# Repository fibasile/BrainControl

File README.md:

BrainControl
============

Arduino Mind Controlled Robot

Bill of materials
-----------------

- Arduino UNO + Arduino PRO Mini
- MindWave Mobile Bluetooth EEG Headset
- Adafruit Neopixel Ring
- Adafruit LED Matrix
- BlueSmirf Silver Bluetooth
- Pololu Zumo Shield

You can find the PCB schematics in the hardware folder along with files for milling.
You can also build this as a breadboard.

Plans for the lasercut box are included in PDF Format.

Finally the sketches BrainControl and RobotControl must be flashed to the two Arduinos.

License
-------

The MIT License (MIT)

Copyright (c) 2014 Fiore Basile

Permission is hereby granted, free of charge, to any person obtaining a copy
of this software and associated documentation files (the "Software"), to deal
in the Software without restriction, including without limitation the rights
to use, copy, modify, merge, publish, distribute, sublicense, and/or sell
copies of the Software, and to permit persons to whom the Software is
furnished to do so, subject to the following conditions:

The above copyright notice and this permission notice shall be included in
all copies or substantial portions of the Software.

THE SOFTWARE IS PROVIDED "AS IS", WITHOUT WARRANTY OF ANY KIND, EXPRESS OR
IMPLIED, INCLUDING BUT NOT LIMITED TO THE WARRANTIES OF MERCHANTABILITY,
FITNESS FOR A PARTICULAR PURPOSE AND NONINFRINGEMENT. IN NO EVENT SHALL THE
AUTHORS OR COPYRIGHT HOLDERS BE LIABLE FOR ANY CLAIM, DAMAGES OR OTHER
LIABILITY, WHETHER IN AN ACTION OF CONTRACT, TORT OR OTHERWISE, ARISING FROM,
OUT OF OR IN CONNECTION WITH THE SOFTWARE OR THE USE OR OTHER DEALINGS IN
THE SOFTWARE.

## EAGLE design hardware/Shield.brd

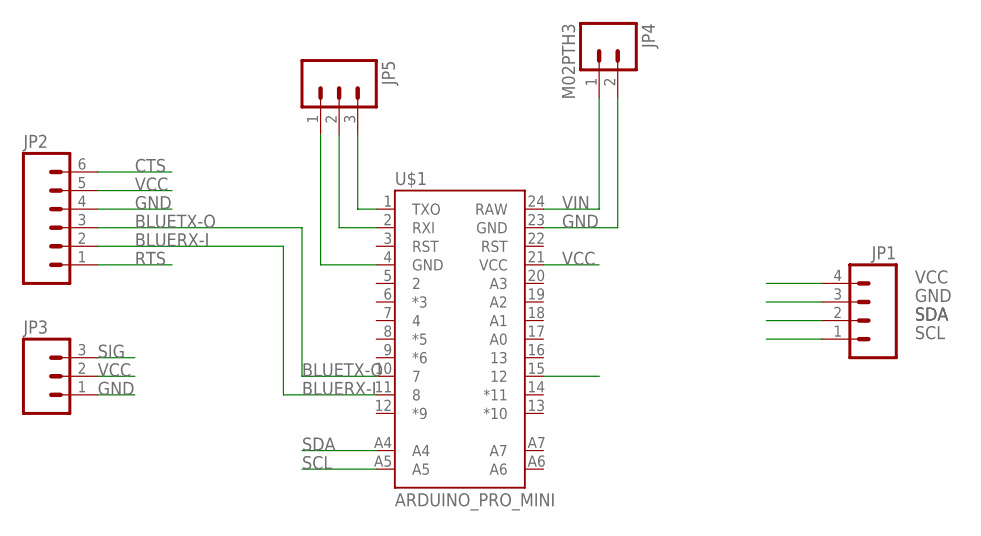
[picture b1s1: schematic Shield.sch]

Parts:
JP1: M04LONGPADS; 1X04_LONGPADS
JP2: M06LONGPADS; 1X06_LONGPADS
JP3: M03PTH; 1X03
JP4: M02PTH3; 1X02_LONGPADS
JP5: M03LONGPADS; 1X03_LONGPADS
U$1: ARDUINO_PRO_MINI

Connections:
BLUERX-I: JP2.2, U$1.11 (8)
BLUETX-O: JP2.3, U$1.10 (7)
CTS: JP2.6
GND: JP1.3, JP2.4, JP3.1, JP4.2, JP5.1, U$1.4 (GND), U$1.23 (GND)
RTS: JP2.1
RX-I: JP5.2, U$1.2 (RXI)
SCL: JP1.1, U$1.A5
SDA: JP1.2, U$1.A4
SIG: JP3.3, U$1.15 (12)
TX-O: JP5.3, U$1.1 (TXO)
VCC: JP1.4, JP2.5, JP3.2, U$1.21 (VCC)
VIN: JP4.1, U$1.24 (RAW)

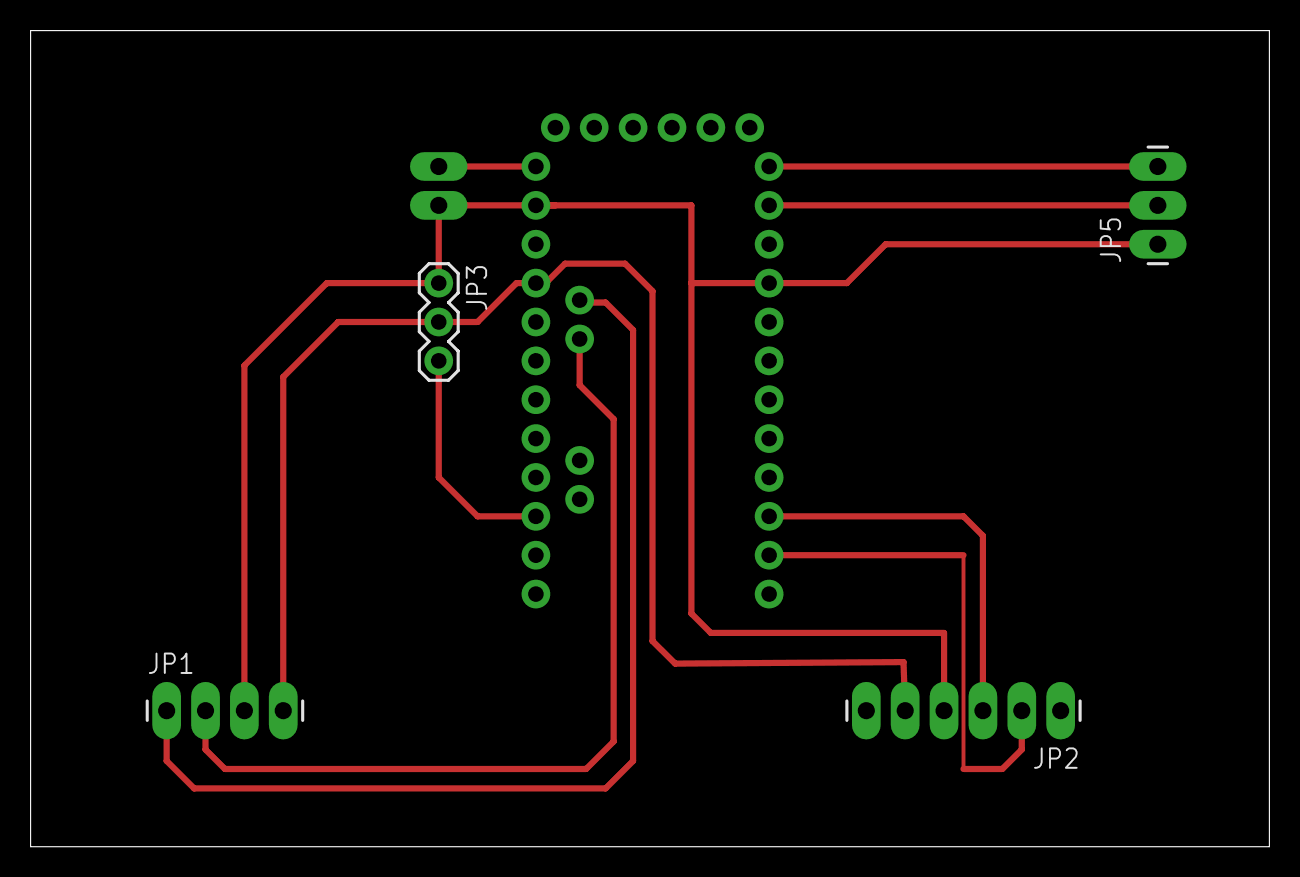
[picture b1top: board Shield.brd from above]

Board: 2 copper layers, 81.0 x 53.3 mm, 6 parts (1 on the bottom side), 10 nets.

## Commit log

2014-06-20 initial import

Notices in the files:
parts and their libraries:
SparkFun-Boards: Licensing: Creative Commons ShareAlike 4.0 International - https://creativecommons.org/licenses/by-sa/4.0
